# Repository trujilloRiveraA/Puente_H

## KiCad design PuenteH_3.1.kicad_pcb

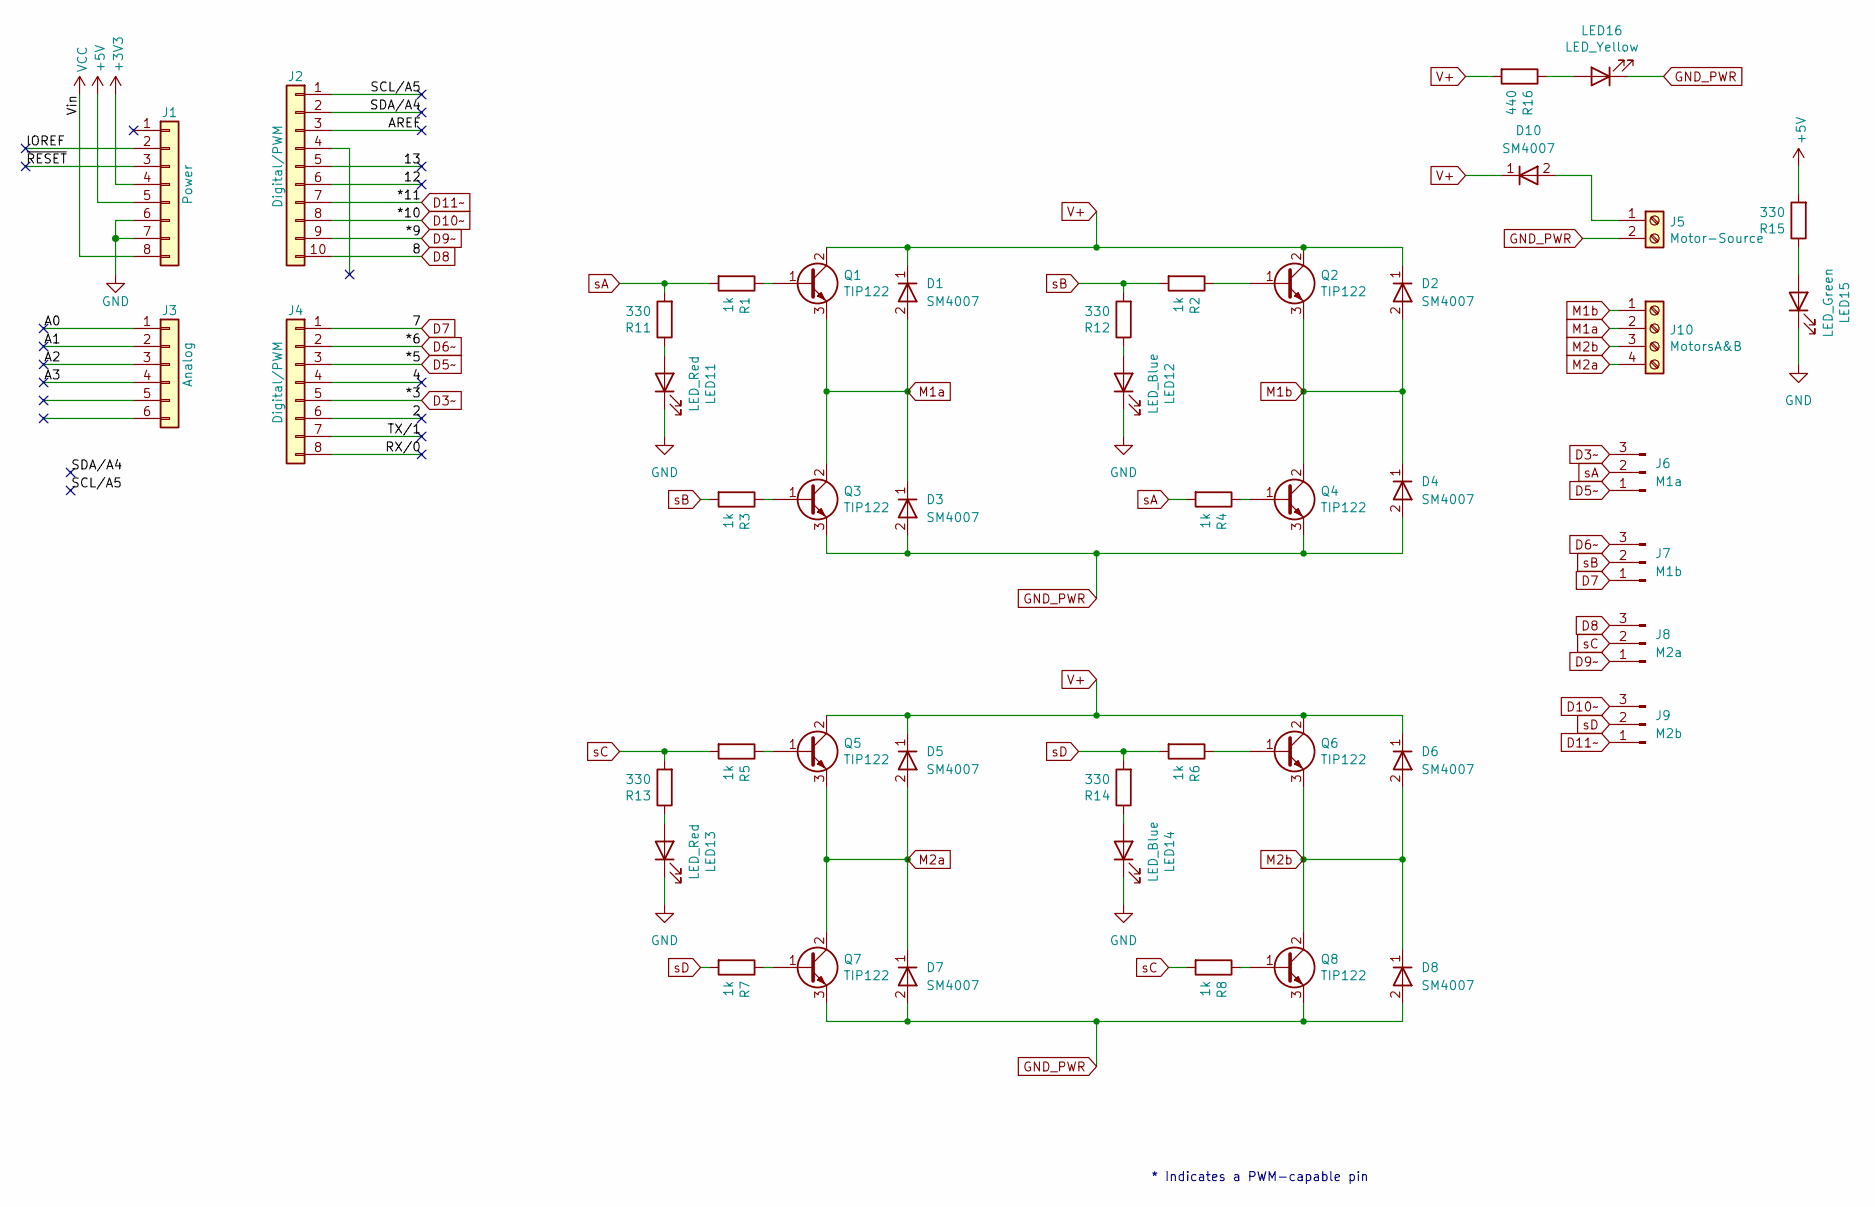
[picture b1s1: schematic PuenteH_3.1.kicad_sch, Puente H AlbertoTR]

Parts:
D1, D2, D3, D4, D5, D6, D7, D8, D10: SM4007; D_SOD-123
J1: Power; PinSocket_1x08_P2.54mm_Vertical
J2: Digital/PWM; PinSocket_1x10_P2.54mm_Vertical
J3: Analog; PinSocket_1x06_P2.54mm_Vertical
J4: Digital/PWM; PinSocket_1x08_P2.54mm_Vertical
J5: Motor-Source; TerminalBlock_Altech_AK300-2_P5.00mm
J6: M1a; PinHeader_1x03_P2.54mm_Vertical
J7: M1b; PinHeader_1x03_P2.54mm_Vertical
J8: M2a; PinHeader_1x03_P2.54mm_Vertical
J9: M2b; PinHeader_1x03_P2.54mm_Vertical
J10: MotorsA&B; TerminalBlock_Altech_AK300-4_P5.00mm
LED11, LED13: LED_Red; LED_0603_1608Metric_Pad1.05x0.95mm_HandSolder; LCSC Part # C72041
LED12, LED14: LED_Blue; LED_0603_1608Metric_Pad1.05x0.95mm_HandSolder; LCSC Part # C72041
LED15: LED_Green; LED_0603_1608Metric_Pad1.05x0.95mm_HandSolder; LCSC Part # C72041
LED16: LED_Yellow; LED_0603_1608Metric_Pad1.05x0.95mm_HandSolder; LCSC Part # C72041
Q1, Q2, Q3, Q4, Q5, Q6, Q7, Q8: TIP122; TO-252-2; LCSC Part # C59488
R1, R2, R3, R4, R5, R6, R7, R8: 1k; R_0603_1608Metric_Pad0.98x0.95mm_HandSolder; LCSC Part # C21190
R11, R12, R13, R14, R15: 330; R_0603_1608Metric_Pad0.98x0.95mm_HandSolder; LCSC Part # C23138
R16: 440; R_0603_1608Metric_Pad0.98x0.95mm_HandSolder; LCSC Part # C23138

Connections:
+3V3: J1.4
+5V: J1.5, R15.2
/2: J4.6
/4: J4.4
/12: J2.6
/13: J2.5
/A0: J3.1
/A1: J3.2
/A2: J3.3
/A3: J3.4
/AREF: J2.3
/IOREF: J1.2
/RX/0: J4.8
/SCL/A5: J2.1
/SDA/A4: J2.2
/TX/1: J4.7
/~RESET: J1.3
D3~: J4.5, J6.3
D5~: J4.3, J6.1
D6~: J4.2, J7.3
D7: J4.1, J7.1
D8: J2.10, J8.3
D9~: J2.9, J8.1
D10~: J2.8, J9.3
D11~: J2.7, J9.1
GND: J1.6, J1.7, LED11.1 (K), LED12.1 (K), LED13.1 (K), LED14.1 (K), LED15.1 (K)
GND_PWR: D3.2 (A), D4.2 (A), D7.2 (A), D8.2 (A), J5.2, LED16.1 (K), Q3.3 (E), Q4.3 (E), Q7.3 (E), Q8.3 (E)
M1a: D1.2 (A), D3.1 (K), J10.2, Q1.3 (E), Q3.2 (C)
M1b: D2.2 (A), D4.1 (K), J10.1, Q2.3 (E), Q4.2 (C)
M2a: D5.2 (A), D7.1 (K), J10.4, Q5.3 (E), Q7.2 (C)
M2b: D6.2 (A), D8.1 (K), J10.3, Q6.3 (E), Q8.2 (C)
unnamed: D10.2 (A), J5.1
unnamed: LED11.2 (A), R11.1
unnamed: LED12.2 (A), R12.1
unnamed: LED13.2 (A), R13.1
unnamed: LED14.2 (A), R14.1
unnamed: LED15.2 (A), R15.1
unnamed: LED16.2 (A), R16.1
unnamed: Q1.1 (B), R1.1
unnamed: Q2.1 (B), R2.1
unnamed: Q3.1 (B), R3.1
unnamed: Q4.1 (B), R4.1
unnamed: Q5.1 (B), R5.1
unnamed: Q6.1 (B), R6.1
unnamed: Q7.1 (B), R7.1
unnamed: Q8.1 (B), R8.1
V+: D1.1 (K), D2.1 (K), D5.1 (K), D6.1 (K), D10.1 (K), Q1.2 (C), Q2.2 (C), Q5.2 (C), Q6.2 (C), R16.2
VCC: J1.8
sA: J6.2, R1.2, R4.2, R11.2
sB: J7.2, R2.2, R3.2, R12.2
sC: J8.2, R5.2, R8.2, R13.2
sD: J9.2, R6.2, R7.2, R14.2

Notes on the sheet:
* Indicates a PWM-capable pin

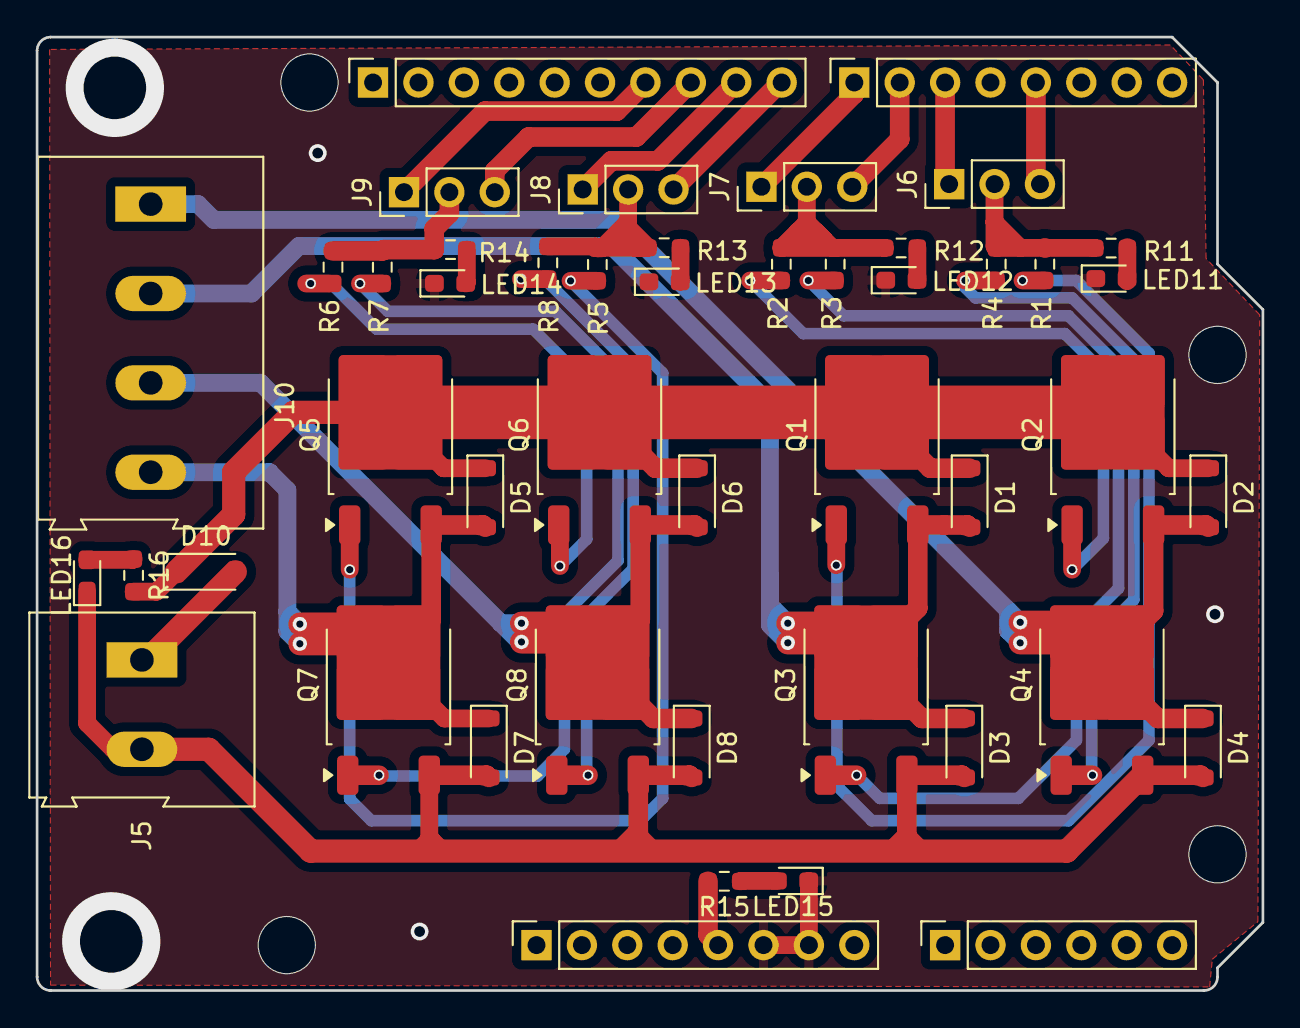
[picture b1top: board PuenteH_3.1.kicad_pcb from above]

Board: 2 copper layers, 68.6 x 53.3 mm, 51 parts (0 on the bottom side), 35 nets.

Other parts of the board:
MH1, MH2, MH3, MH4: MountingHole_3.2mm

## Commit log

2025-07-19 SMD Footprint assigned
